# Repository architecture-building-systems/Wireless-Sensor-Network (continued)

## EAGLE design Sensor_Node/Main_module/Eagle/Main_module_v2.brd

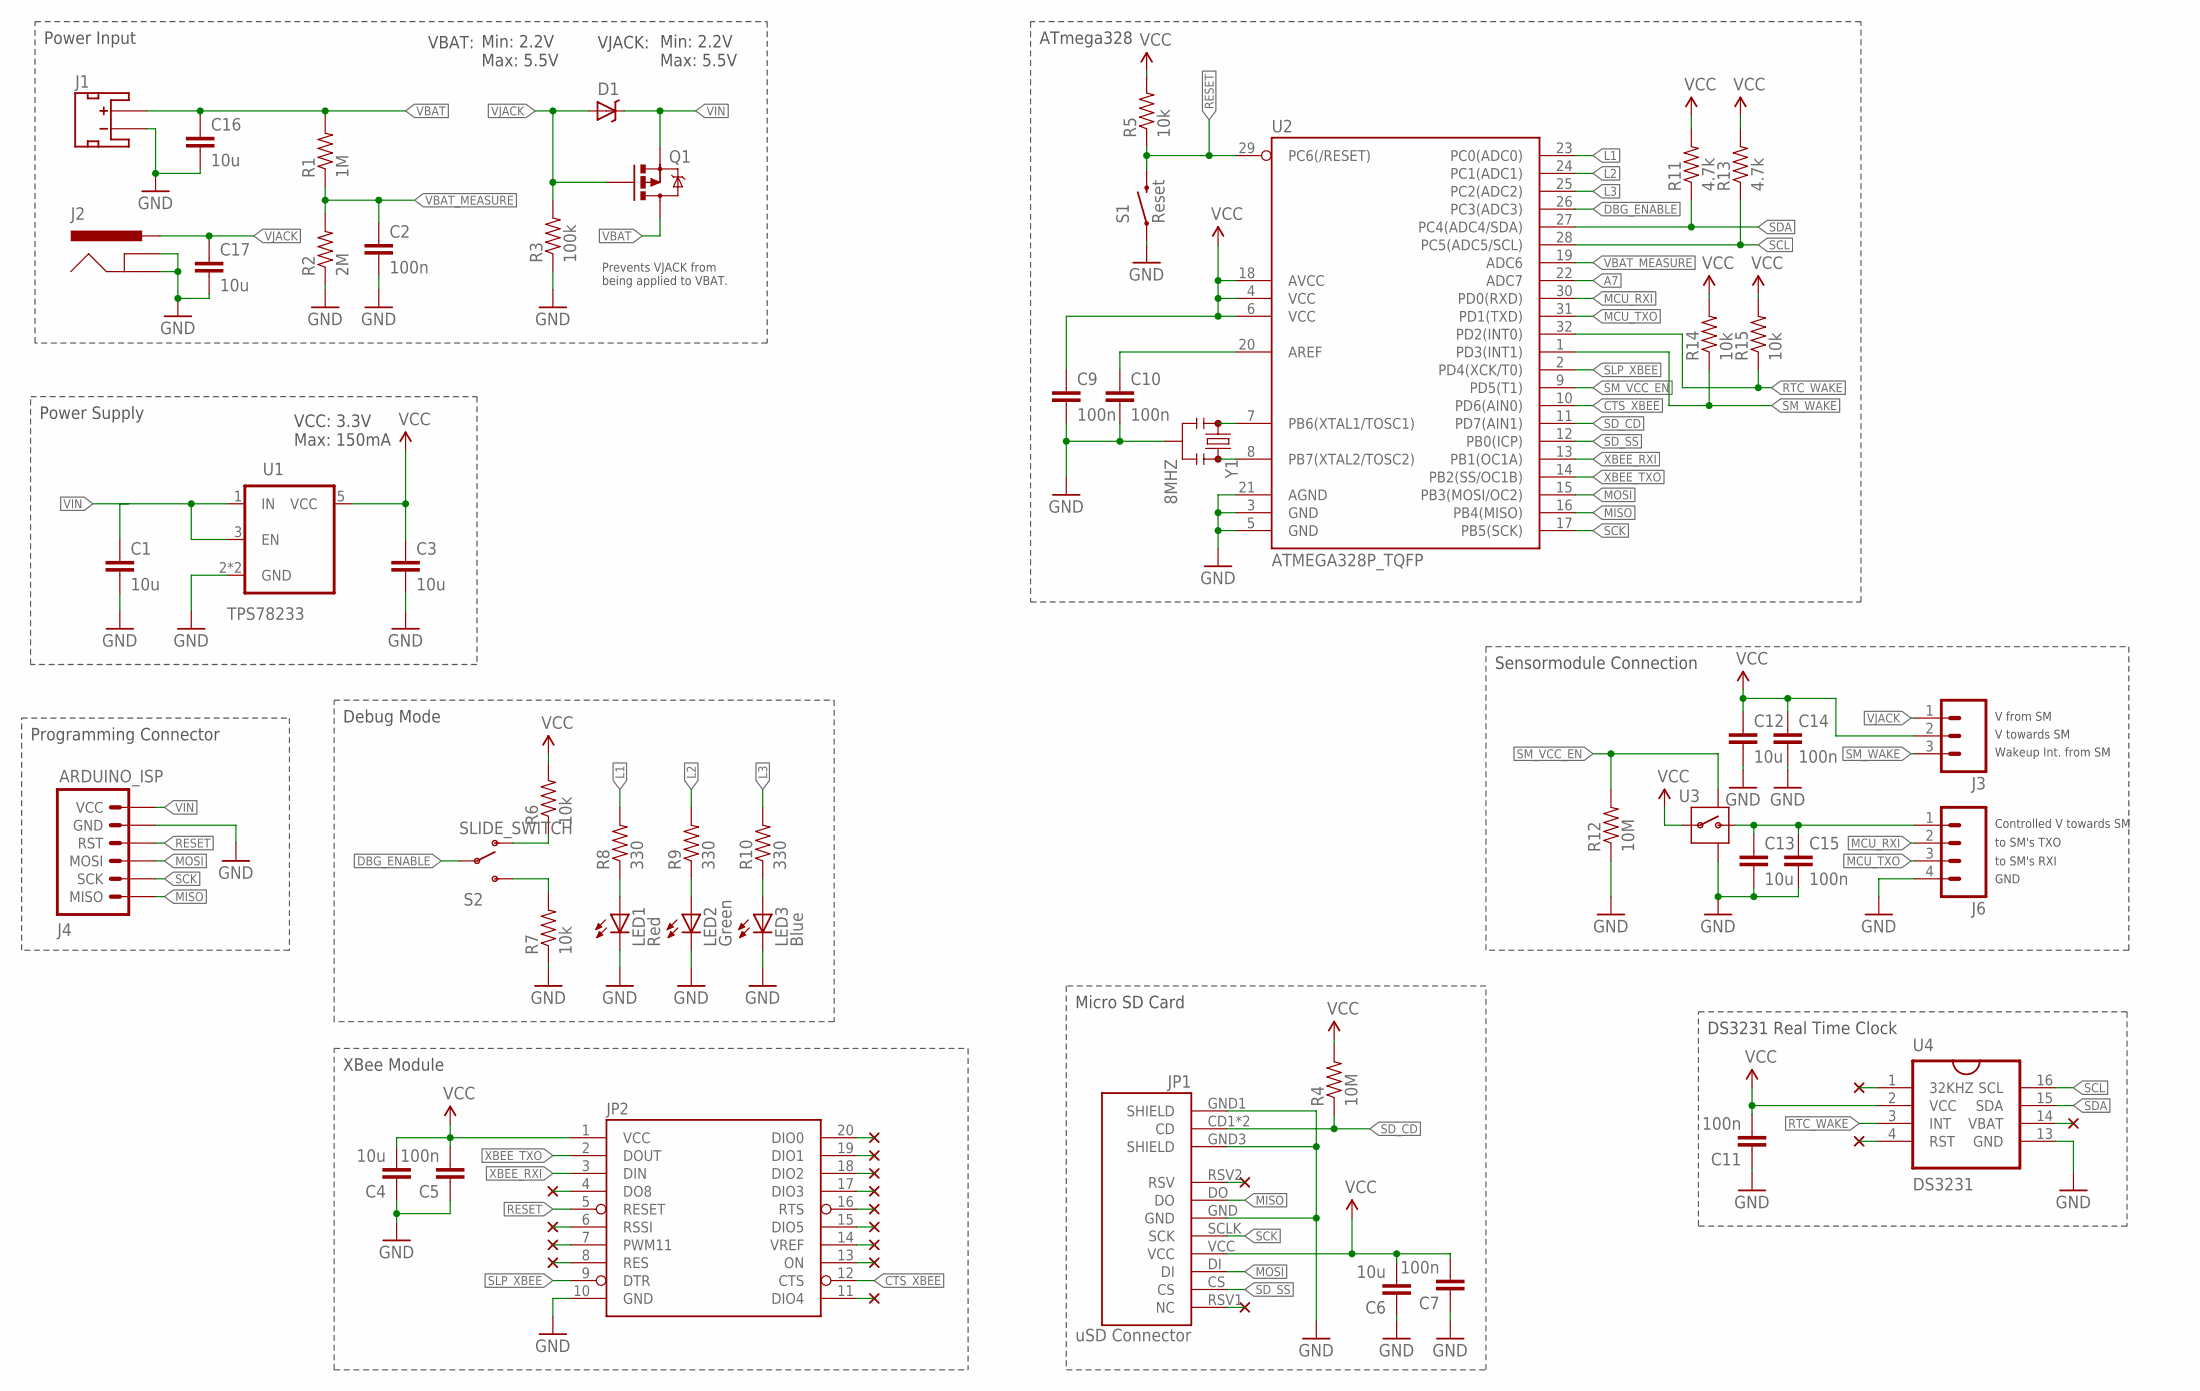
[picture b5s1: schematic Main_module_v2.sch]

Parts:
C1, C3, C4, C6, C12, C13, C16, C17: 10u; C0805
C2, C5, C7, C9, C10, C11, C14, C15: 100n; C0805
D1: DIODE-SCHOTTKY; 0603-DIODE
J1: JST_2MM_MALE; JST-2-SMD
J2: 5.5x2.1mm Barrel; POWER_JACK_SMD
J3: M03PTH; 1X03
J4: ARDUINO_ISP; M-2X3
J6: M04PTH; 1X04
JP1: USD-SOCKETNEW; MICRO-SD-SOCKET-PP
JP2: XBEEB3; XBEE-SMD
LED1: Red; SML0805
LED2: Green; SML0805
LED3: Blue; SML0805
Q1: PFET; SOT23-3
R1: 1M; 0805
R2: 2M; 0805
R3: 100k; 0805
R4, R12: 10M; 0805
R5, R6, R7, R14, R15: 10k; 0805
R8, R9, R10: 330; 0805
R11, R13: 4.7k; 0805
S1: Reset; M-PUSHBUTTON-SMD
S2: SLIDE_SWITCH; P-JS202011SCQN
U1: TPS78233; SOT23-5
U2: ATMEGA328P_TQFP; TQFP32-08
U3: SIP32431; SC70
U4: DS3231SOIC16; SO016
Y1: 8MHZ; RESONATOR-SMD

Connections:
A7: U2.22 (ADC7)
CTS_XBEE: JP2.12 (CTS), U2.10 (PD6(AIN0))
DBG_ENABLE: S2.P$2 (MIDDLE), S2.P$5 (MIDDLE), U2.26 (PC3(ADC3))
GND: C1.2, C2.2, C3.2, C4.1, C5.1, C6.1, C7.1, C9.2, C10.2, C11.1, C12.2, C13.2, C14.2, C15.2, C16.2, C17.2, J1.1 (-), J2.GND (GNDBREAK), J2.P$4 (GND), J4.P$5 (GND), J6.4, JP1.GND, JP1.GND1 (SHIELD), JP1.GND3 (SHIELD), JP2.10 (GND), LED1.C, LED2.C, LED3.C, R2.1, R3.1, R7.1, R12.1, S1.1 (LEFT), S1.2 (LEFT), U1.2 (GND), U1.4 (GND), U2.3 (GND), U2.5 (GND), U2.21 (AGND), U3.2 (GND), U3.5 (GND), U3.6 (GND), U4.13 (GND), Y1.2
L1: R8.2, U2.23 (PC0(ADC0))
L2: R9.2, U2.24 (PC1(ADC1))
L3: R10.2, U2.25 (PC2(ADC2))
MCU_RXI: J6.2, U2.30 (PD0(RXD))
MCU_TXO: J6.3, U2.31 (PD1(TXD))
MISO: J4.P$1 (MISO), JP1.DO, U2.16 (PB4(MISO))
MOSI: J4.P$3 (MOSI), JP1.DI, U2.15 (PB3(MOSI/OC2))
unnamed: U2.8 (PB7(XTAL2/TOSC2)), Y1.3
unnamed: U2.7 (PB6(XTAL1/TOSC1)), Y1.1
unnamed: LED3.A, R10.1
unnamed: LED2.A, R9.1
unnamed: C13.1, C15.1, J6.1, U3.1 (OUT)
unnamed: C10.1, U2.20 (AREF)
unnamed: LED1.A, R8.1
unnamed: R7.2, S2.P$1 (LOWER), S2.P$4 (LOWER)
unnamed: R6.1, S2.P$3 (UPPER), S2.P$6 (UPPER)
RESET: J4.P$4 (RST), JP2.5 (RESET), R5.1, S1.3 (RIGHT), S1.4 (RIGHT), U2.29 (PC6(/RESET))
RTC_WAKE: R15.1, U2.32 (PD2(INT0)), U4.3 (INT)
SCK: J4.P$2 (SCK), JP1.SCLK (SCK), U2.17 (PB5(SCK))
SCL: R13.1, U2.28 (PC5(ADC5/SCL)), U4.16 (SCL)
SDA: R11.1, U2.27 (PC4(ADC4/SDA)), U4.15 (SDA)
SD_CD: JP1.CD1 (CD), JP1.CD2 (CD), R4.1, U2.11 (PD7(AIN1))
SD_SS: JP1.CS, U2.12 (PB0(ICP))
SLP_XBEE: JP2.9 (DTR), U2.2 (PD4(XCK/T0))
SM_VCC_EN: R12.2, U2.9 (PD5(T1)), U3.3 (ON)
SM_WAKE: J3.3, R14.1, U2.1 (PD3(INT1))
VBAT: C16.1, J1.2 (+), Q1.3 (D), R1.2
VBAT_MEASURE: C2.1, R1.1, R2.2, U2.19 (ADC6)
VCC: C3.1, C4.2, C5.2, C6.2, C7.2, C9.1, C11.2, C12.1, C14.1, J3.2, JP1.VCC, JP2.1 (VCC), R4.2, R5.2, R6.2, R11.2, R13.2, R14.2, R15.2, U1.5 (VCC), U2.4 (VCC), U2.6 (VCC), U2.18 (AVCC), U3.4 (IN), U4.2 (VCC)
VIN: C1.1, D1.C, J4.P$6 (VCC), Q1.2 (S), U1.1 (IN), U1.3 (EN)
VJACK: C17.1, D1.A, J2.VIN0 (PWR), J2.VIN1 (PWR), J3.1, Q1.1 (G), R3.2
XBEE_RXI: JP2.3 (DIN), U2.13 (PB1(OC1A))
XBEE_TXO: JP2.2 (DOUT), U2.14 (PB2(SS/OC1B))

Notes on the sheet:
Min: 2.2V Max: 5.5V
VCC: 3.3V Max: 150mA
Sensormodule Connection
Debug Mode
Power Supply
Micro SD Card
Programming Connector
XBee Module
DS3231 Real Time Clock
ATmega328
Prevents VJACK from being applied to VBAT.
VJACK:
VBAT:
Power Input
V towards SM
V from SM
Wakeup Int. from SM
Controlled V towards SM
to SM's TXO
to SM's RXI
GND

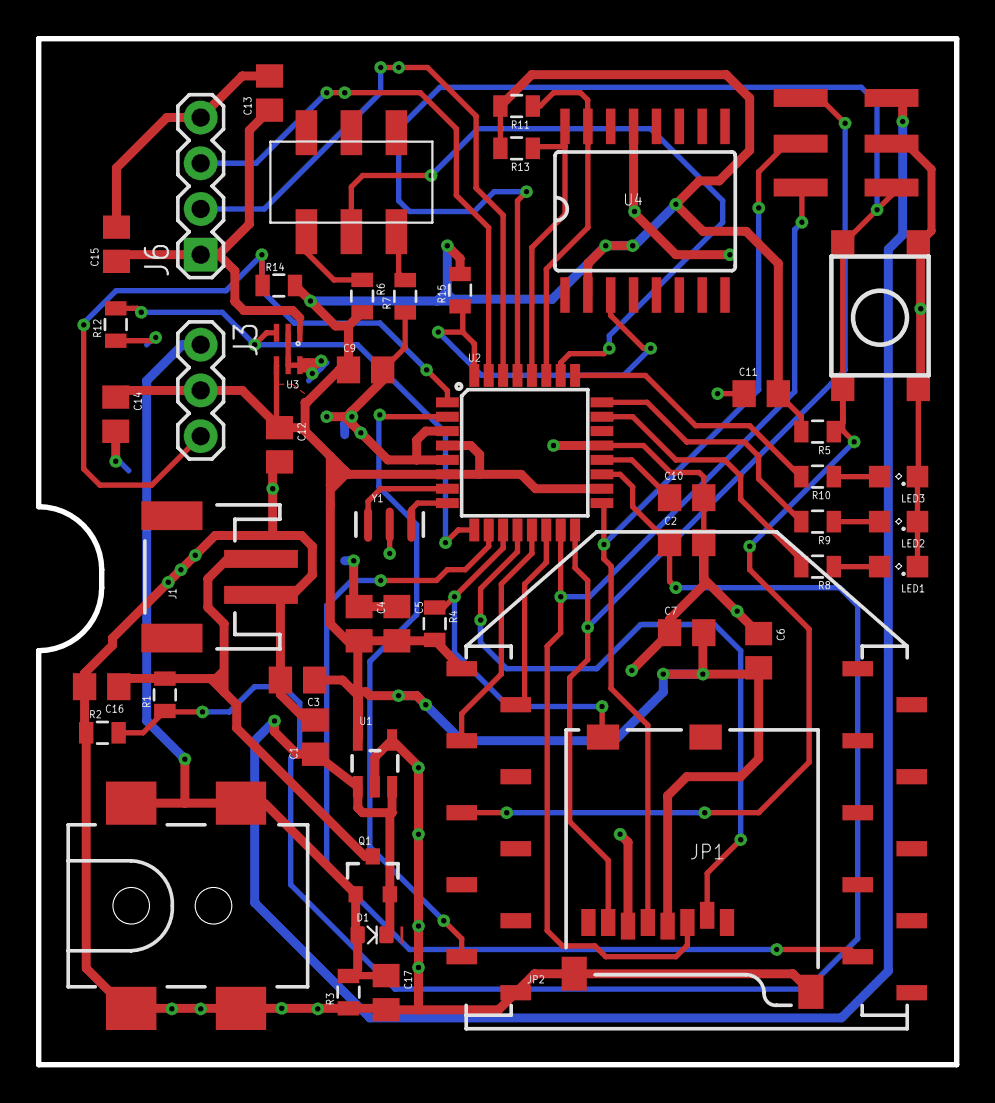
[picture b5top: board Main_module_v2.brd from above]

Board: 2 copper layers, 51.0 x 57.0 mm, 50 parts (0 on the bottom side), 36 nets.

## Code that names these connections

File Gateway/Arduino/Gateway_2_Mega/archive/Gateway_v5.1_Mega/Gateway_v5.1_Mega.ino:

/*******************************************
 * Gateway Arduino Sketch v5.1             *
 * Author: Mario Frei                      *
 * Sources: FONA library FONAtest sketch  *
 *           Xbee library example sketch   *
 *******************************************/

int gatewayID = 1;                                         // Set this accordingly
String serverURL = "http://[your webserver].ch/wsn/gateway2mysql.php";  // Instert the url to your web server here
bool resetFlag = true;

// Libraries
#include "Adafruit_FONA.h"
#include <SoftwareSerial.h>
#include <XBee.h>
#include <avr/wdt.h>  // Remember USB-Serial doesn't work after first reset.

// Debugging
#define LED_PIN 3
int counter = 0;

// FONA
#define FONA_RX 2
#define FONA_TX 10   
#define FONA_RST 22  
#define FONA_RI 53
//("gprs.swisscom.ch", "gprs", "gprs");  // Configure a GPRS APN, username, and password.
#define APN F("gprs.swisscom.ch")        // Change this according to your providers instructions
#define APN_USR F("gprs")
#define APN_PWD F("gprs")
SoftwareSerial fonaSS = SoftwareSerial(FONA_TX, FONA_RX);
SoftwareSerial *fonaSerial = &fonaSS;
Adafruit_FONA fona = Adafruit_FONA(FONA_RST);// Use this one for FONA 3G: //Adafruit_FONA_3G fona = Adafruit_FONA_3G(FONA_RST);
uint8_t readline(char *buff, uint8_t maxbuff, uint16_t timeout = 0);

// Xbee
XBee xbee = XBee();
XBeeResponse response = XBeeResponse();
// create reusable response objects for responses we expect to handle 
ZBRxResponse rx = ZBRxResponse();
ModemStatusResponse msr = ModemStatusResponse();

String payload;




/*********************
 * Setup             *
 *********************/
void setup() {
// Initialize serial connection --------------------------------------------------------
  Serial.begin(9600);
  Serial.println("Serial initialized");
  
// Initialize Xbee ---------------------------------------------------------------------
  Serial3.begin(9600);
  xbee.setSerial(Serial3);
  Serial.println("Xbee initialized");
  
// Initialize Fona ---------------------------------------------------------------------
  fonaSerial->begin(4800);
  if (! fona.begin(*fonaSerial)) {
    Serial.println("FONA not OK");
    while (1);
  }
  Serial.println("FONA OK");
  Serial.println("Wait for Call Ready & SMS Ready messages");
  delay(14000); // Wait for "Call Ready" & "SMS Ready" messages
  while (fona.available()) {
      Serial.write(fona.read());
  }
  // turn GPRS on
  startGPRS();
  Serial.println("FONA initialized");

// Debugging
  Serial.println("End Setup");
  blink(10);
}


/*********************
 * Loop              *
 *********************/
void loop() {
// Debugging ---------------------------------------------------------------------------
  Serial.println(counter++);
  delay(1500);
  blink(2);
  
// If Xbee message available, retrieve it-----------------------------------------------
    xbee.readPacket();
    if (xbee.getResponse().isAvailable()) {// got something
      if (xbee.getResponse().getApiId() == ZB_RX_RESPONSE) {// got a zb rx packet
        payload = getXbeePacket();
//  -> send to webserver ---------------------------------------------------------------
        send2Server();
        resetFlag = false;
        blink(5);
        }
    }
}


/*********************************************
 * Retrieve Xbee packet                      *
 *********************************************/
String getXbeePacket(){
    // now fill our zb rx class
    xbee.getResponse().getZBRxResponse(rx);   
    unsigned char payload[rx.getDataLength()];      
    for (int i = 0; i < rx.getDataLength(); i++) {
      payload[i] = char(rx.getData()[i]);
    }
    char payloadCharArray[sizeof(payload)*3+1];
    for (int i=0; i < sizeof(payload); i++){
      hex2char(payloadCharArray, i*3, byte(payload[i]));
      payloadCharArray[i*3+2] = '.';
    }
    payloadCharArray[sizeof(payloadCharArray)-1] = '\0';
    return payloadCharArray;
}


/*********************************************
 * Send2Server                               *
 *********************************************/
bool send2Server()
{
  uint16_t statuscode;
  int16_t length;
  String url; 
  url  = serverURL;
  url += "?payload=";
  url += payload;
  url += "&g_id=";
  url += gatewayID;
  if (resetFlag){
    url += "&comment=Reset";
  }
  
  char urlCharArray [url.length()+1];
  url.toCharArray(urlCharArray, url.length()+1);
  
  if (!fona.HTTP_GET_start(urlCharArray, &statuscode, (uint16_t *)&length)) {
    // Failed to send: Resetting uC, FONA library will reset FONA
    reset();
  }
  else {
    fona.HTTP_GET_end();
  }
  return true;
}


/*********************************************
 * hex2char                                  *
 *********************************************/
void hex2char(char* charArray, int index, byte theNumber){
  charArray[index] = (theNumber >> 4) + 0x30;
  if (charArray[index] > 0x39) charArray[index] +=7;
  charArray[index+1] = (theNumber & 0x0f) + 0x30;
  if (charArray[index+1] > 0x39) charArray[index+1] +=7;
  return;
}


/**************************************************
 * enable GPRS                                    *
 **************************************************/
void startGPRS(){
  fona.setGPRSNetworkSettings(APN, APN_USR, APN_PWD);  // Configure a GPRS APN, username, and password.
  if (!fona.enableGPRS(true))
  {
    Serial.println(F("GPRS failed"));
  } else{
    Serial.println(F("GPRS on"));
  }
}

 
/**************************************************
 * LED Blink                                      *
 **************************************************/
void blink(int n){
  int T = 75;
  for (int i=0; i<n; i++){
    pinMode(LED_PIN, OUTPUT);
    digitalWrite(LED_PIN, HIGH);
    delay(T);
    digitalWrite(LED_PIN, LOW);
    delay(T);
  }
}


/**************************************************
 * Reset                                          *
 *************************************************/
// Remember, the USB-serial doesn't work anymore after first reset.
void reset(){
  // Turn FONA library does a hard reset, therefore resetting FONA seperatly is not necessary
  Serial.println(F("Resetting"));
  // Reset Microcontroller
  wdt_enable(WDTO_15MS);         // WDTO_15MS, 30MS, 60MS, 120MS, 250MS, 500MS, 1S, 2S, 4S, 8S
}

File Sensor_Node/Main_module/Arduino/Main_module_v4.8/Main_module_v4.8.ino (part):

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static const uint8_t P_CTS_XBEE     = 6; // Input, XBee's clear to send pin
static const uint8_t P_SD_CD        = 7; // Input, detect whether SD card is inserted
static const uint8_t P_SD_SS        = 8; // Output, slave select pin for SD card SPI
static const uint8_t P_XBEE_RXI     = 9; // Serial communication RXI pin for Xbee
static const uint8_t P_XBEE_TXO     = 10;// Serial communication TXO pin for Xbee
static const uint8_t P_MOSI         = 11;// SPI MOSI pin
static const uint8_t P_MISO         = 12;// SPI MISO pin
static const uint8_t P_SCK          = 13;// SPI SCK pin
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
void endSerialToSM() {
  // End serial connection to sensor module
  // If Serial.end() is not called, the MCU_TXO pin stays at high voltage level
  Serial.end();

  // Pins low
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
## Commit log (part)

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2017-03-10 added readme
2017-03-10 Add Xbee-Profiles
2017-03-10 Removed archive folder from xbee-profiles
2017-03-10 Added some Eagle files
2017-03-10 Add router node cad files
2017-03-10 Added gateway cad files
2017-03-10 Changed Router-node cad files names
2017-04-14 Added U-value boards
2017-04-18 Added lots of files
    - Added Arduino scripts
    - Added Eagle schematics and layouts
    - Added PHP files
    - New name scheme for folders and files
2017-04-19 Added CAD-files of xbee-grabbing-tool
2017-05-01 Revert "kgu"
    This reverts commit f6d5939cbe47795ed7e9f89d86337f994c9aab1c.
2017-05-01 Revert "Changed something"
    This reverts commit e7fad535a0aed3b7ca3650d1b08948d39ff050b6.
2017-05-01 Changes on SensModule TSL2561
    - removed R11
    - added pogohead programming connector
2017-05-01 Changes on SensModule SHT31
    - removed R4
    - added pogopin programming connector
2017-05-01 Changes on SensModule 2xDS18B20
    - added pogopin programming connector
2017-05-01 Changes on SensModule CO2 S8
    - added poppin programming connector
    - moved communication connectors closer together
    - turned C3
2017-05-01 Changes on SensModule Pulse
    - moved connectors closer together
    - turned various components
    - added pogopin programming connector
    - removed digital input jumper and put digi_input 1 and 2 directly to
    PD2, PD3
    - put wakeup on PC1
2017-05-02 Changes on all boards
    - added capacitor on reset-path
    - changed order of pogopin programmer pins
    Pulse-Board:
    - Deleted input-jumper. Currently one interrupt-pin missing, so print is
    not yet routed.
2017-05-08 Added SensModule Prototyping_Board
    - almost finished
2017-05-09 Added 3D printing parts for sensor node
2017-05-09 Moved sensor node cad-files
2017-05-09 Changed some SensorBoards
    SHT31
    - new routing
    PULSE
    - pogopin programmer now over FTDI
    - interrupt to comboard now comes from atmega
    TSL2561
2017-05-10 Updated schematic description
2017-05-15 Finished some boards.
    - Minor changes on all boards except
2017-06-14 Added PDFs of Eagle files
2017-06-14 Added project description
    modified readme file
2017-06-14 Typo fix on readme.md
2017-06-14 Fixed typo in readme.md
2017-06-15 Fixed to grammar issues in readme.md
2017-06-15 added .b$? eagle files to gitignore
2017-06-19 Added dustpan cad-file
2017-06-19 Update WSN Eagle library
2017-06-19 Update U-Value board, Added Readme for sensor boards
2017-06-30 Updated gatway board, updated u-value board
2017-07-06 Added missing RTC functions
2017-07-25 Simplification of communication board Arduino script
2017-08-02 Added 8Pin, 90°, SMD male Pinheader
2017-08-02 Added SMD pin headers to gateway board
2017-08-02 minor changes to gateway eagle files
2017-08-02 Removed gap between connectors to commBoard, added power jack
2017-08-02 Removed gap between connector to commBoard
2017-08-02 Removed gap between connectors to commBoard
2017-08-06 SHT31
    - reset path
    - sensor connector footer
2017-08-06 TSL2561
    - reset path
    - sensor connector footer
2017-08-06 Pulse-Board
    - Reset path
    - Various small things
2017-08-06 DS18B20 - Board
    - adjusted reset path
    - minor changes in layout
2017-08-06 Prototype - Board
    - reset path
    - minor changes
2017-08-08 Renamed U-value sensor board files
2017-08-18 Update gateway documentation
2017-08-22 Added images of sensor-kit
2017-09-12 Error TSL2561
    Rotated the sensor connector by 180 deg.
2017-10-26 Changed Sensorboard TSL2561
    - adjusted connector of comboard to a consistent distance
2017-11-06 Changes on PulseBoard
    - startet replacement and rerouting
    - corrected faulty VCC-Connection
2017-11-06 Finished Changes on PulseBoard
    Pulseboard:
    - tidied up routing and placement
    TSL2561:
    - tidied up some connections
2017-11-06 Started tidying of SHT31
2017-11-16 Finished SHT31 and CO2-Board
    - finished tidying SHT31
    - added FTDI-connector to CO2-Sensorboard
    - tidied CO2-Sensorboard
2017-11-23 Updated Prototyping Board & DS18B20 Board
2017-12-03 Finished Prototyping Board
    - did some tyding up
2017-12-11 Vorlage-Board
2017-12-11 Updated PDFs
2017-12-11 Started C02-Board v2
    - SMD C02-Sensor
    - SMD SHT31
2017-12-13 Updated CO2-Board
2017-12-15 Changed folder-naming of CO2-Board v2
2017-12-15 Added Sensor Board TLS2561 v2
2017-12-16 Uploaded Testcode for CO2-Board v2
2018-01-10 Added CAD files for cable reel
    The cable reels helps keeping the sensor cables tidy.
2018-01-10 Changed diameter of reel
2018-01-17 Added CAD files for battery storage box
2018-01-17 Modified battery strage box (CAD)
2018-01-20 Corrected mistake on C02-Board
    -Connected enable-pin of sensor to GND
2018-01-20 Various changes
    - updated two masks
    - changed combined mask again
    - tiedied up CO2 sensor a bit
    - used another footprint for TSL2561-sensor
2018-01-22 Added Images of communication board and sensor node
2018-01-23 Updated readme for routers
2018-01-23 Moved XBee profile files for coordinator from commBoard to Gateway
2018-01-23 Added XBee settings to readme for gateways
2018-01-23 Fixed link
2018-01-23 Rename Router_Node/Xbee_Profiles/Router_R18x.xml to Router_Node/XBee_Profiles/Router_R18x.xml
2018-01-23 added dummy file
2018-01-23 Issue with Xbee/XBee _Profiles directory (remove to readd)
2018-01-26 Added different versions of battery box for test-printing
2018-01-29 Changed label on silk screen of SHT31 sensor board
2018-01-29 Added gerber files for sensor boards
2018-01-30 Update battery box cad files
2018-02-02 added images for webserver stuff
2018-02-04 Improved cable reel (v2 & v3)
2018-02-04 added missing chamfer
2018-02-06 Update battery box
2018-02-06 Moved files to archive directory
2018-02-06 Allow directories named "archive"
2018-02-21 Renamed folder of sensor boards for pulse reading
2018-02-21 Added Arduino skript for sensor board interfacing a water meter
2018-02-21 Update water flow meter arduino skript
2018-02-28 Small changes to CO2/SHT31 - Testscode
2018-03-12 Opened new Projekt for Heat Flux v2
    - should be based on Atmega
2018-03-12 Added corners on the bottom part
2018-03-17 Added some function tests for the new boards
2018-05-23 Moved tutorials.md to repo wiki
2018-05-23 Added BOM
2018-05-23 Added new Gateway versions (with improved integrety against signal interference)
2018-05-23 Added temporary excel files to .gitignore
2018-05-30 Update BOM
2018-06-01 Work on heat flux sensor continued
2018-06-11 Worked on heat flux board
2018-07-03 Finished routing of heat flux v2
2018-07-10 Weiterarbeit Heat Flux
2018-07-10 Finished sensorboard heat flux v2
    - added BOM
    - added PDF's
2018-07-11 Added gerber files to u-value board
2018-07-24 Renamed Heat_Flux to U-Value
2018-07-24 Added functionality tests for U-Value board
    With the 100_measurement example, we get an offset of about 7mV to a Fluke 289 when measuring the same voltage on a breadboard.
2018-08-03 Rename boards to modules
    Rename sensor boards / communication boards to sensor module and main module
2018-08-03 Rename boards to modules
2018-08-03 Rename sensor board to sensor module
2018-08-03 Rename files (board ->module)
2018-08-03 Speed up Web GUI
2018-08-03 Add execution time to web gui
2018-08-24 Add test scripts for gateway
2018-08-24 Update FONA gateway
2018-09-20 Added some images
2018-09-20 Added script for Uno and Mega variants of the gateway
2018-09-20 Changed image in the readme document
2018-10-07 Changes to gateway mega housing
2018-10-25 Changes on example code for uV-Sensor
    - Renamed existing codes
    - Added a new Functiontest that implements GAIN and OFFSET calibration
2018-10-31 Various changes in arduino-codes
    - added libraries to the sensor-boards
    - small changes in codes
    - deleted old, redundant codes
2018-11-09 config.php: all configurations are now in one file
2018-11-16 removed url from images
2018-11-16 Added brief setup instructions for the webserver
2018-11-16 fixed broken link
2018-11-16 Clean up of php files
2018-11-16 Added links
2018-11-16 Reduced images size in read.me
2018-11-16 Removed leftover from table
2018-11-16 fixed typo
2018-11-19 Add access token check
2018-11-19 Add script for external access of plots (with access token)
2018-11-27 Update gateway mega housing
2018-11-27 rename arduino script
2018-11-27 Added note about other gateway versions
2018-11-27 Rename gateway-eagle directory
2018-11-27 Add new gateway script / Clean up folder structure
2018-11-28 Changed to main module arduino code
    The original code from Marc was added (v0).
    Three lines needed to be changed in v0: (->v2_2018)
    - turnOffSensorModule(); // Line 440
    - ()>>8; // Line 567
    - attachInterrupt(1, pin3_isr, RISING); // Line 1095
    Additionaly the addresses of our xbee modules set as coordinators were added for convienient flashing.
2018-12-06 Added 3D models for utlities
2018-12-07 Add sensor modules for flow meter interface
2018-12-07 Added class for sensor module payload generation
2018-12-07 Updated template script for sensor modules
2018-12-12 Shorten file names
2018-12-14 Added documents for deployment
2018-12-14 Edited tools and materials list
2019-01-11 Small changes to debugging output, added 1 line of comments
2019-01-12 Transport container: Adjustment to outer dimensions
2019-01-23 Add code for Keyence flow meter
2019-01-30 adjusted dimensions of tape container
2019-02-08 Added new RTC dates
2019-02-08 changed default max flow rate
2019-03-29 add new timestamps to gateway mega script
2019-03-29 fix pins of arduino mkr
2019-05-08 Update mysql database structure
    A database updated required to define the the default values in the tables. Otherwise, insertions were no longer possible.
2019-05-08 Shorten directory names and file names
2019-05-08 Rename Functiontest_0x02_Temperature_Humidity_SHT31_v2.ino to _0x02_TH_SHT31_v2.inoFunctiontest
2019-09-20 Add APN info for "sunrise"
2019-09-20 Add eagle files for proper shield for "Gateway Mega"
2019-09-20 Add documentation from marc for main module
2019-10-24 Modify sparkfun arduino mega shield
2019-10-31 Simplify main module code
    - remove sd card functionality
    - remove concatenation of multiple measurements
    - remove code fragements
    - add blink()
2019-11-01 Add payload class for main module
2019-11-01 Simplify main module code
    - heart beat message (RSSI, battery charge level)
    - low battery warning as standard payload
    - remove sd card functionality
    - remove out commented code
2019-11-05 Add improvement suggestions
2019-11-05 Fix reporting interval of heartbeat message
2019-11-05 Add RSSI and battery readout to gateway
2019-11-25 Add images for assembly
2019-12-03 Adapt low battery warning on server for man modul firmware version 4.7+
2019-12-03 Fix heartbeat
2019-12-06 fix heartbeat interval
2019-12-06 Add cross-site scripting warning
2019-12-06 minor formatting change
2019-12-12 Add main_module_v4.8
    // Improvements from v4.7
    // - Check debug switch only once in the setup function (tested)
    // - Remove debug_mode_has_been_switched_off (tested)
    // - Implement universal coordinator address (tested)
    // - Replace THIS_CM_ID by MAIN_MODULE_ID (tested)
    // - Apply payload class to standard measurement payload (tested)
2020-01-19 Update publications
2020-02-17 Clean up directories
2020-02-17 Add link to wiki
2020-02-25 add images for instructions
2020-02-25 change filename
2020-02-25 rename files (id->ide)
2020-03-02 Add images from predecessor systems
2020-03-05 clean up directory hierarchy for gateways
2020-03-05 add images for gateway mega
2020-03-05 remove readme.md in gateway directory
2020-03-05 Remove readme.md in sensor node directory
    the same information is available in the wiki
2020-03-05 Remove links to readme.md files
2020-03-09 Create export.php
    add web interface for exporting measurement data
2020-03-09 export measurement data for list of node_ids or from campaign_name
2020-03-09 remove debugging output
2020-03-09 update example
2020-03-11 minor formatting stuff
2020-03-13 Added requirement for fix
2020-05-18 Add zenodo shield
2020-07-17 Change file paths for includes add debugging messages
2020-07-17 Add initial sensor_module_type data for database
2020-07-17 update URL on gateway
2020-07-17 add token check to isituprightnow_v5
